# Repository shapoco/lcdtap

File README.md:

A library and its example design that receives LCD controller commands (via SPI or I2C)
and outputs the framebuffer as a DVI-D signal.

## Overview

See [introduction page](https://shapoco.github.io/lcdtap/).

## Implementations

### [LcdTap-Pico2 Universal](example/pico2_universal/)

Supports multiple LCD controllers (ST7789, ILI9341, SSD1306, SSD1331, ST7032)
and interfaces, selectable at runtime via an OSD menu.

### [LcdTap-Pico2W Remote](example/pico2w_remote/)

Raspberry Pi Pico 2 W version with no video output: the captured screen is
read over WiFi through an HTTP JSON API and a built-in web UI
(`http://lcdtap.local/`). WiFi setup via the
[Remote Setup page](https://shapoco.github.io/lcdtap/remote/) (WebSerial).

## License

MIT License — see [LICENSE](LICENSE).

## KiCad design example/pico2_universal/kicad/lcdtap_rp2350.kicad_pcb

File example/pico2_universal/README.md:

# LcdTap-Pico2 Universal

A universal LCD-to-DVI converter example for Raspberry Pi Pico 2. With an OSD (On-Screen Display) menu for runtime configuration.

## Features

- Supports four input interfaces selectable via OSD: I2C, 4-Line SPI, 3-Line SPI, 8-bit Parallel
- Runtime configuration via OSD menu: interface, controller type, pixel format, LCD size, inversion, R/B swap, rotation, scale mode
- Settings (including selected interface) saved to flash on Apply and restored at next boot
- DVI output: 640×480@60Hz or 1280×720@30Hz selectable via GPIO21 at boot
- Composite video output (NTSC/PAL) on otherwise-unused GPIOs, selectable from the OSD: a 1-pin PWM DAC or a 7-bit R-2R ladder
- DisplayLink output: drives a USB graphics adapter (DisplayLink DL-1x0/1x5) at 1280×720 or 1920×1080@60Hz via a PIO USB Full-Speed host on GPIO10/11 (best-effort update rate)
- USB CDC serial interface for remote configuration and framebuffer readout from a PC or smartphone

> [!WARNING]
> Parallel Mode has not been tested yet. Please let me know if it works!

## Schematics

- Keep the input bus as short as possible and ensure all cables are the same length.
- See also: [Recommended Header Pinout](https://shapoco.github.io/lcdtap/#header_pinout)

## GPIO Assignments

### Common (all modes)

| GPIO  | Direction | Name | Active-low | Internal Pull-up | Description |
|:--:|:--:|:--|:--:|:--:|:--|
| 0     | IN        | RST | v | v | LCD Hardware reset (SPI mode) |
| 5–11  | OUT       | CVBS_D[0..6] | | | Composite R-2R ladder (SPI modes only, when selected) |
| 10    | OUT       | CVBS_PWM | | | Composite PWM output (SPI/I2C, when selected) |
| 10/11 | I/O       | USB_DP / USB_DM | | | DisplayLink USB host D+/D- (SPI/I2C, when selected) |
| 12–19 | OUT       | (DVI signals) | | | RP2350 HSTX |
| 20    | IN        | CFG_OUT_RESO_SEL | v | v | High=640×480@60Hz,<br>Low=1280×720@30Hz |
| 21    | IN        | KEY_DOWN | v | v | Low=pressed |
| 22    | IN        | KEY_LEFT | v | v | Low=pressed |
| 26    | IN        | KEY_UP | v | v | Low=pressed |
| 27    | IN        | KEY_RIGHT | v | v | Low=pressed |
| 28    | IN        | KEY_ENTER | v | v | Low=pressed |

### I2C Mode

| GPIO  | Direction | Name | Active-low | Internal Pull-up | Description |
|:--:|:--:|:--|:--:|:--:|:--|
| 8     | IN        | SDA | | v | I2C data |
| 9     | IN        | SCL | | v | I2C clock |

### 4-Line/3-Line SPI Mode

| GPIO  | Direction | Name | Active-low | Internal Pull-up | Description |
|:--:|:--:|:--|:--:|:--:|:--|
| 1     | IN        | CS | v | v | LCD Chip select |
| 2     | IN        | SCLK | | | SPI clock from master |
| 3     | IN        | MOSI | | | SPI data from master |
| 4     | IN        | DC | | | D/C# signal from master (4-line mode only) |

### Parallel Mode

| GPIO  | Direction | Name | Active-low | Internal Pull-up | Description |
|:--:|:--:|:--|:--:|:--:|:--|
| 1 | IN | CS | v | v | LCD Chip select|
| 2 | IN | WR | | | Write strobe |
| 3–10 | IN | D[0..7] | | | parallel data |
| 11 | IN | DC | | | D/C# signal |

For text displays, connect the R/W signal to CS and the E signal to WR.

For KS0108-compatible displays (such as SG12864), connect CS1 to RST,
CS2 to CS, and AND the inverted R/W signal with the E signal to connect to WR.
If R/W is fixed to Low, you can connect the E signal directly to the WR terminal.

## Composite Video Output (NTSC/PAL)

The HDMI connector occupies GPIO12–19, so composite video uses the GPIOs that
the input bus leaves free. Two independent OSD items control it (or
`outputInterface` / `compositeDac` over USB CDC):

- **`Output`** — `DVI-D`, `NTSC` or `PAL`
- **`Composite DAC`** — `PWM` or `R-2R`

There are therefore two quality tiers, and you only build the one you want:

| DAC | GPIO | Parts | Picture | Buses |
|:--|:--|:--|:--|:--|
| **PWM** | 10 | 1 resistor + 1 capacitor | ~12 luma steps, ~70% amplitude | SPI, I2C |
| **R-2R** | 5–11 | 14 resistors, no buffer | 7-bit luma, full amplitude | SPI only |

The R-2R ladder spans GPIO5–11, which covers the I2C pins (GPIO8/9), so it is
selectable only on SPI; the OSD greys it out otherwise. Composite output is
unavailable on the parallel bus entirely — GPIO3–10 are data lines there, which
covers the PWM pin too.

**The device resets** when `Output` changes (each mode needs a different system
clock), and when the bus or the DAC changes while a composite mode is running.

PAL colour is not implemented yet; PAL currently outputs monochrome on both
DACs.

> [!NOTE]
> Both DACs share GPIO10, so the two circuits are alternative populations, not
> simultaneous ones. Build whichever tier you want.

### PWM DAC — simple tier

One GPIO, one resistor, one capacitor. No buffer.

```
GPIO10 --- R ---+--- RCA centre
                |
                C
                |
               GND
```

The PWM period equals the sample period, so the duty resolution *is* the
sample period in system clocks: 22 steps on NTSC, 17 on PAL. White sits at
duty 17/22 rather than 100%, because chroma overshoots white by up to
+133 IRE and has to fit above it.

That, plus the 12 mA per-pin limit, is why the amplitude falls short of the
1 V standard — a single 3.3 V GPIO simply cannot reach it:

| R | White level | Sync amplitude | Peak current |
|:--|:--|:--|:--|
| 120 Ω | 0.78 V (78%) | 0.23 V (80%) | 13.5 mA |
| **150 Ω** | **0.70 V (70%)** | **0.21 V (72%)** | **12.0 mA** |
| 180 Ω | 0.63 V (63%) | 0.18 V (64%) | 10.8 mA |

Start at **R = 150 Ω** and drop to 120 Ω if a receiver refuses to lock.
Most TVs slice sync on the AC-coupled signal and tolerate this; capture
devices are less forgiving. C = 100–470 pF (corner ≈ 5–6 MHz).

The PWM carrier sits at 14.3 MHz with chroma at 3.58 MHz — only two octaves
apart — so a single-pole RC leaves visible carrier ripple. That is the
accepted cost of this tier.

### R-2R ladder — quality tier

The ladder drives the 75 Ω line **directly, with no buffer**. To deliver the
~1 V composite range into 75 Ω, its output impedance has to be low, so the
resistors are ~10× smaller than a textbook ladder: **R = 100 Ω series, 2R =
200 Ω rungs, 200 Ω termination.**

The firmware drives GPIO5 as the **LSB** and GPIO11 as the **MSB** (the PIO
maps sample bit 0 to the lowest GPIO). In an R-2R ladder the bit nearest the
output node has the greatest weight, so the **output is tapped at the GPIO11
(MSB) end** and the termination sits at the GPIO5 (LSB) end. Sync tip is 0 V at
the ladder, so it connects straight to the RCA centre — no coupling capacitor.

```
GPIO11 -- 200R --+---------------- RCA centre       (MSB, weight 64)
        (MSB)    |            |
               100R        (470pF)   optional reconstruction
                |            |        cap to GND (~6 MHz)
GPIO10 -- 200R --+          GND
                 :   (GPIO9, 8, 7, 6 identical)
               100R
                |
GPIO5  -- 200R --+                                  (LSB, weight 1)
        (LSB)    |
               200R    (2R termination)
                |
               GND
```

Wiring it the other way round — output at GPIO5, termination at GPIO11 —
reverses the bit weights and scrambles the picture, so double-check the
orientation.

2R = 200 Ω keeps the exact 2:1 R-2R ratio against the 100 Ω series resistor,
and in practice gives the most stable picture. The termination is another
200 Ω, so every rung and the termination share the same value.

Peak GPIO current is ~13 mA — just over the nominal 12 mA, which is fine here.
The drive strength stays at 12 mA (set in firmware).

> [!NOTE]
> These are a bench starting point. With a scope on a **50 % grey** field,
> confirm the mid-scale step is clean and monotonic.
>
> With nominal values the levels come out a few percent high (full scale
> ~1.4 V, white ~1.1 V, blanking ~0.3 V; sync tip 0 V). Trim this by scaling
> all three resistor families up together, or just leave it — the receiver
> works on relative levels. **Do not** retune it with `lvlWhite` / `lvlBlank`
> in `composite_timing.cpp`: those are shared with the PWM DAC. Use 1 %
> resistors, and keep 2R = 200 and the termination = 200 as a matched set.

## DisplayLink Output (USB)

Select `DisplayLink` as the `Output` (or `outputInterface = 3` over USB CDC) to
drive a USB graphics display adapter instead of the HDMI connector. The
adapter is driven by a PIO-based USB **Full-Speed** host
([Pico_USB_Disp](https://github.com/htlabnet/Pico_USB_Disp)) on GPIO10 (D+)
and GPIO11 (D−), so only the **DisplayLink DL-1x0 / DL-1x5** generation
works — newer chips (DL-3xxx and later) require High-Speed and encrypted
protocols. 1920×1080 needs a DL-165 or DL-195; smaller chips automatically
fall back to 1280×720.

- **Resolution** follows the CFG_OUT_RESO_SEL pin: open = 1280×720@60Hz,
  low = 1920×1080@60Hz (the DVI 480p/720p slots map to 720p/1080p).
- The adapter scans out a stable 60 Hz signal from its own framebuffer; the
  Pico streams **best-effort partial updates** over the ~1 MB/s bulk link.
  Only lines whose pixel values actually changed are re-sent, so mostly
  static screens update quickly; a full-screen change takes on the order of
  0.3–1 s (tearing can occur — there is no vsync over USB).
- Unavailable on the parallel bus (GPIO10/11 are D[7] and D/C# there), and
  mutually exclusive with the composite DACs, which share GPIO10.

Hardware: wire a USB-A receptacle with **5 V bus power (500 mA class)** to
the adapter, D+/D− to GPIO10/11. The 3.3 V GPIO levels match USB FS
signalling directly; series damping resistors up to ~47 Ω are tolerable at
Full-Speed (22–27 Ω preferred).

## Uploading Firmware

1. Download zip file from [releases](https://github.com/shapoco/lcdtap/releases).
2. Extract `lcdtap_pico2_universal.uf2` from the zip file.
3. Connect the Pico 2 to your computer while holding the BOOTSEL button to enter bootloader mode.
4. Copy the UF2 file to the mounted drive.

## OSD Menu

Press the Enter key to open the configuration menu.

| Key | Action |
|-----|--------|
| Up / Down | Navigate menu items |
| Left / Right | Adjust selected value |
| Enter on Apply | Apply changes and save to flash |
| Enter on Cancel | Discard changes and close |
| Enter on Command Dump | Open the command dump viewer |

### Command Dump Viewer

Selecting **Command Dump** opens a hex viewer that shows the raw LCD command/data stream captured since power-on (or since the last trigger).

| Key | Action |
|-----|--------|
| Enter | Clear buffer and start a new capture |
| Right | Stop capture (mark complete) |
| Left | Return to the configuration menu |
| Up / Down | Scroll |

Each row displays 16 entries. Colors indicate the type of each entry:

| Color | Meaning |
|-------|---------|
| Black on cyan | Command byte |
| White on black / dark-gray (alternating) | Data byte |
| Black on yellow (`HR`) | Hardware reset event |
| `..` in dark gray | Empty (not yet captured) |

## USB Serial Interface

LcdTap-Pico2 Universal accepts JSON commands over the USB CDC serial interface.
This allows remote configuration and framebuffer readout from a PC.

Available here: https://shapoco.github.io/lcdtap/monitor

## Building Firmware from Source

```bash
export PICO_SDK_PATH=/path/to/pico-sdk
./build.sh
```

The UF2 file is generated at `build/lcdtap_pico2_universal.uf2`.

### CMake Options

| Option | Default | Description |
|--------|---------|-------------|
| `LCDTAP_LCD_SIZE_W` | 240 | Initial LCD framebuffer width (px) |
| `LCDTAP_LCD_SIZE_H` | 320 | Initial LCD framebuffer height (px) |

Example:

```bash
cmake .. -DCMAKE_BUILD_TYPE=Release -DPICO_BOARD=pico2 \
         -DLCDTAP_LCD_SIZE_W=320 -DLCDTAP_LCD_SIZE_H=240
```

## External Deserializer for High-Speed SPI

The SPI interface of LcdTap-Pico2 Universal can support clock frequencies up to approximately 50MHz. For frequencies exceeding this, you can add an external deserializer outside the Pico2 to support higher speeds. In this case, select Parallel as the Interface in the OSD menu.

## Troubleshooting

### Failed to boot normally

Try powering on or resetting while pressing the Left key. This will boot while ignoring the settings saved in flash.

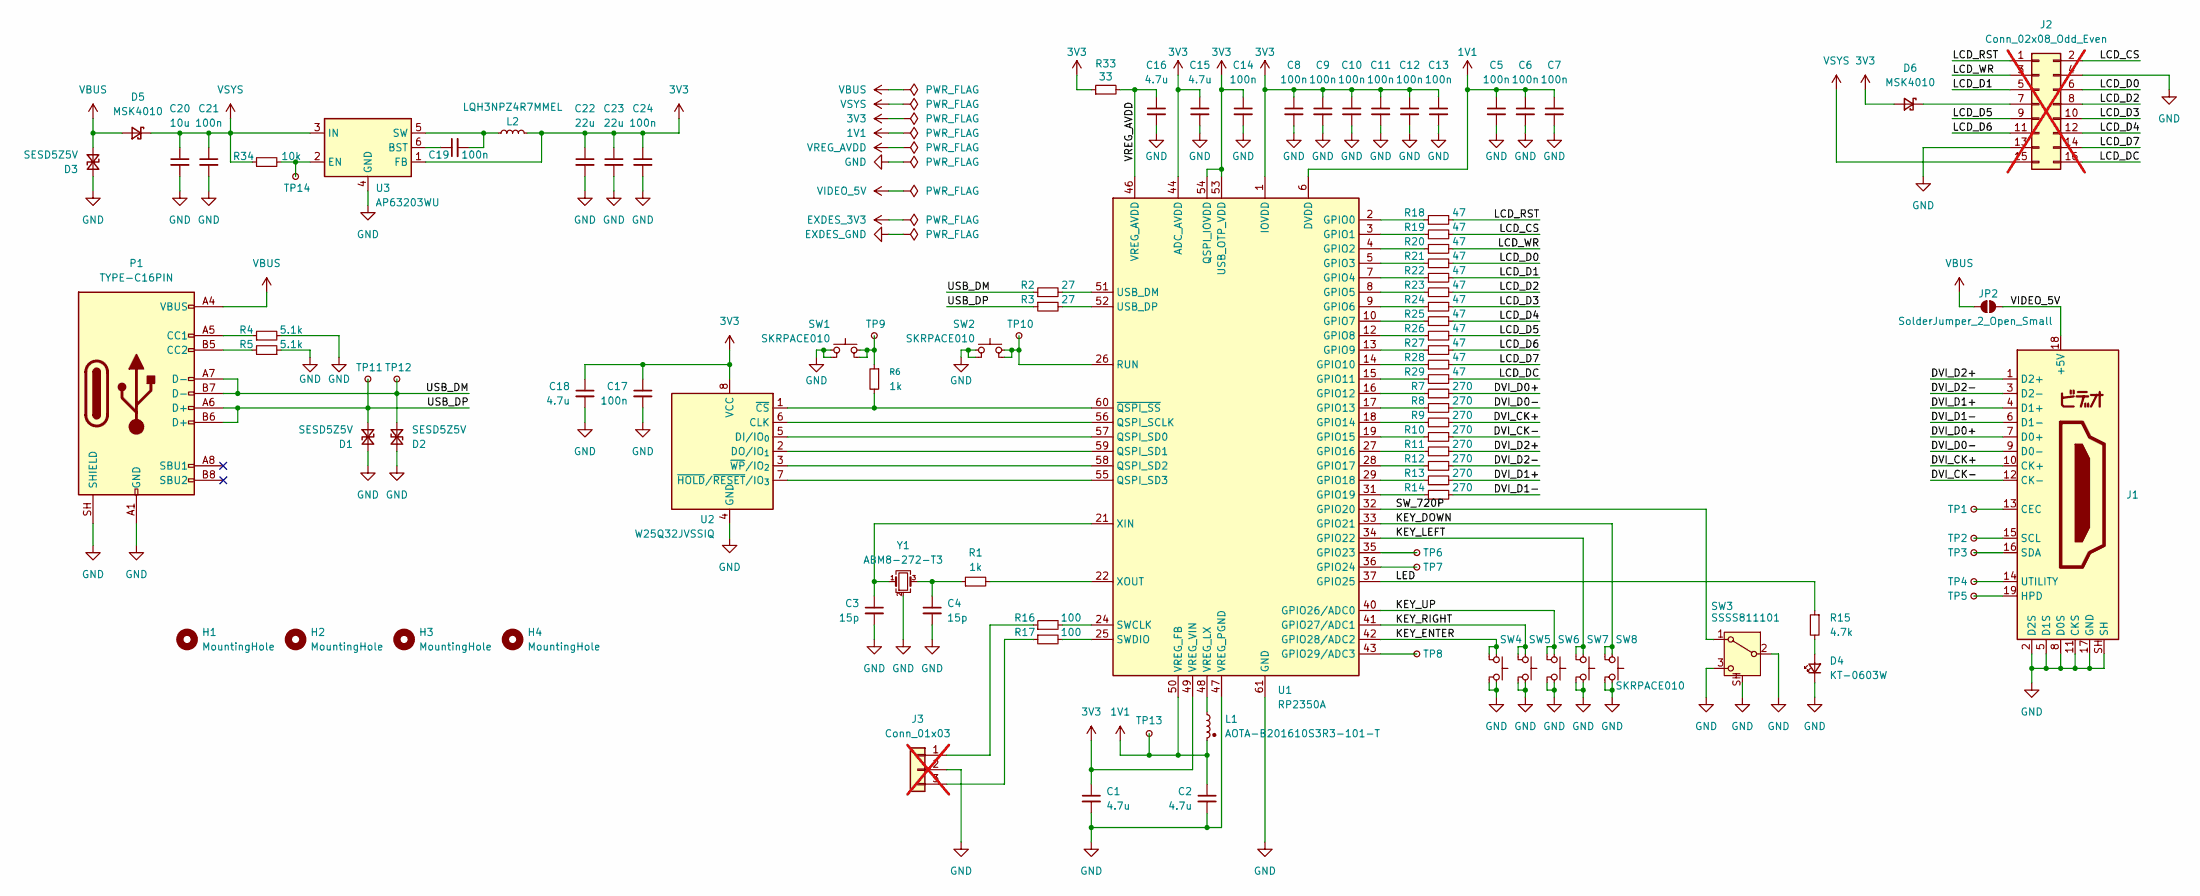
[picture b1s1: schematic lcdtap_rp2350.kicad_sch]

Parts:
C1, C2, C15, C16, C18: 4.7u; C_0603_1608Metric; LCSC C19666
C3, C4: 15p; C_0402_1005Metric; LCSC C1548
C5, C6, C7, C8, C9, C10, C11, C12, C13, C14, C17, C19, C21, C24: 100n; C_0402_1005Metric; LCSC C1525
C20: 10u; C_0603_1608Metric; LCSC C19702
C22, C23: 22u; C_0603_1608Metric; LCSC C59461
D1, D2, D3: SESD5Z5V; D_SOD-523; LCSC C19631222
D4: KT-0603W; LED_0603_1608Metric; LCSC C2290
D5, D6: MSK4010; D_SOD-523; LCSC C282563
H1, H2, H3, H4: MountingHole; MountingHole_3.5mm
J1: HDMI-001S; HDMI_A_Molex_208658-1001_Horizontal_Edge; LCSC C720616
J2: Conn_02x08_Odd_Even; PinHeader_2x08_P2.54mm_Horizontal_Rev; not fitted
J3: Conn_01x03; PinHeader_1x03_P2.54mm_Vertical; not fitted
JP2: SolderJumper_2_Open_Small; SolderJumper-2_P1.3mm_Open_RoundedPad1.0x1.5mm
L1: AOTA-B201610S3R3-101-T; LCSC C42411119
L2: LQH3NPZ4R7MMEL; LCSC C527613
P1: TYPE-C16PIN; USB_C_Receptacle_HCTL_HC-TYPE-C-16P-01A; LCSC C393939
R1, R6: 1k; R_0402_1005Metric; LCSC C11702
R2, R3: 27; R_0402_1005Metric; LCSC C25100
R4, R5: 5.1k; R_0402_1005Metric; LCSC C25905
R7, R8, R9, R10, R11, R12, R13, R14: 270; R_0402_1005Metric; LCSC C25155
R15: 4.7k; R_0402_1005Metric; LCSC C25900
R16, R17: 100; R_0402_1005Metric; LCSC C25076
R18, R19, R20, R21, R22, R23, R24, R25, R26, R27, R28, R29: 47; R_0402_1005Metric; LCSC C25118
R33: 33; R_0402_1005Metric; LCSC C25105
R34: 10k; R_0402_1005Metric; LCSC C25744
SW1, SW2, SW4, SW5, SW6, SW7, SW8: SKRPACE010; SW_Push_1P1T_NO_Vertical_Wuerth_434133025816; LCSC C139797
SW3: SSSS811101; SW_SPDT_Alps_SSSS811101; LCSC C109335
TP1, TP2, TP3, TP4, TP5, TP6, TP7, TP8, TP9, TP10, TP11, TP12, TP13, TP14: TestPoint_Small; TestPoint_Pad_D1.0mm
U1: RP2350A; QFN-60-1EP_7x7mm_P0.4mm_EP3.4x3.4mm; LCSC C42411118
U2: W25Q32JVSSIQ; SOIC-8_5.3x5.3mm_P1.27mm; LCSC C179173
U3: AP63203WU; TSOT-23-6; LCSC C780769
Y1: ABM8-272-T3; Crystal_SMD_3225-4Pin_3.2x2.5mm; LCSC C20625731

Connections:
1V1: C2.1, C5.1, C6.1, C7.1, L1.1, TP13.1 (1_1), U1.6 (DVDD), U1.23 (DVDD), U1.39 (DVDD), U1.50 (VREG_FB)
3V3: C1.1, C8.1, C9.1, C10.1, C11.1, C12.1, C13.1, C14.1, C15.1, C17.1, C18.1, C22.1, C23.1, C24.1, D6.2 (A), L2.1, R33.1, U1.1 (IOVDD), U1.11 (IOVDD), U1.20 (IOVDD), U1.30 (IOVDD), U1.38 (IOVDD), U1.44 (ADC_AVDD), U1.45 (IOVDD), U1.49 (VREG_VIN), U1.53 (USB_OTP_VDD), U1.54 (QSPI_IOVDD), U2.8 (VCC), U3.1 (FB)
/DVI_CK+: J1.10 (CK+), R9.2
/DVI_CK-: J1.12 (CK-), R10.2
/DVI_D0+: J1.7 (D0+), R7.2
/DVI_D0-: J1.9 (D0-), R8.2
/DVI_D1+: J1.4 (D1+), R13.2
/DVI_D1-: J1.6 (D1-), R14.2
/DVI_D2+: J1.1 (D2+), R11.2
/DVI_D2-: J1.3 (D2-), R12.2
/KEY_DOWN: SW8.2, U1.33 (GPIO21)
/KEY_ENTER: SW4.2, U1.42 (GPIO28/ADC2)
/KEY_LEFT: SW7.2, U1.34 (GPIO22)
/KEY_RIGHT: SW5.2, U1.41 (GPIO27/ADC1)
/KEY_UP: SW6.2, U1.40 (GPIO26/ADC0)
/LCD_CS: J2.2, R19.2
/LCD_D0: J2.6, R21.2
/LCD_D1: J2.5, R22.2
/LCD_D2: J2.8, R23.2
/LCD_D3: J2.10, R24.2
/LCD_D4: J2.12, R25.2
/LCD_D5: J2.9, R26.2
/LCD_D6: J2.11, R27.2
/LCD_D7: J2.14, R28.2
/LCD_DC: J2.16, R29.2
/LCD_RST: J2.1, R18.2
/LCD_WR: J2.3, R20.2
/LED: R15.1, U1.37 (GPIO25)
/SW_720P: SW3.1 (A), U1.32 (GPIO20)
/USB_DM: D2.1 (A1), P1.A7 (D-), P1.B7 (D-), R2.1, TP12.1 (1_1)
/USB_DP: D1.1 (A1), P1.A6 (D+), P1.B6 (D+), R3.1, TP11.1 (1_1)
GND: C1.2, C2.2, C3.2, C4.2, C5.2, C6.2, C7.2, C8.2, C9.2, C10.2, C11.2, C12.2, C13.2, C14.2, C15.2, C16.2, C17.2, C18.2, C20.2, C21.2, C22.2, C23.2, C24.2, D1.2 (A2), D2.2 (A2), D3.2 (A2), D4.1 (K), J1.2 (D2S), J1.5 (D1S), J1.8 (D0S), J1.11 (CKS), J1.17 (GND), J1.SH, J2.4, J2.13, J3.2, P1.A1 (GND), P1.A12 (GND), P1.B1 (GND), P1.B12 (GND), P1.SH (SHIELD), R4.2, R5.1, SW1.1, SW2.1, SW3.2 (B), SW3.3 (C), SW3.SH, SW4.1, SW5.1, SW6.1, SW7.1, SW8.1, U1.47 (VREG_PGND), U1.61 (GND), U2.4 (GND), U3.4 (GND), Y1.2 (G), Y1.4 (G)
unnamed: C4.1, R1.1, Y1.3
unnamed: D4.2 (A), R15.2
unnamed: D6.1 (K), J2.7
unnamed: J1.13 (CEC), TP1.1 (1_1)
unnamed: J1.19 (HPD), TP5.1 (1_1)
unnamed: J1.15 (SCL), TP2.1 (1_1)
unnamed: J1.16 (SDA), TP3.1 (1_1)
unnamed: J1.14 (UTILITY), TP4.1 (1_1)
unnamed: J3.1, R16.1
unnamed: J3.3, R17.1
unnamed: P1.A5 (CC1), R4.1
unnamed: P1.B5 (CC2), R5.2
unnamed: R6.1, SW1.2, TP9.1 (1_1)
unnamed: R18.1, U1.2 (GPIO0)
unnamed: R19.1, U1.3 (GPIO1)
unnamed: R20.1, U1.4 (GPIO2)
unnamed: R21.1, U1.5 (GPIO3)
unnamed: R22.1, U1.7 (GPIO4)
unnamed: R23.1, U1.8 (GPIO5)
unnamed: R24.1, U1.9 (GPIO6)
unnamed: R25.1, U1.10 (GPIO7)
unnamed: R26.1, U1.12 (GPIO8)
unnamed: R27.1, U1.13 (GPIO9)
unnamed: R28.1, U1.14 (GPIO10)
unnamed: R29.1, U1.15 (GPIO11)
unnamed: R7.1, U1.16 (GPIO12)
unnamed: R8.1, U1.17 (GPIO13)
unnamed: R9.1, U1.18 (GPIO14)
unnamed: R10.1, U1.19 (GPIO15)
unnamed: R11.1, U1.27 (GPIO16)
unnamed: R12.1, U1.28 (GPIO17)
unnamed: R13.1, U1.29 (GPIO18)
unnamed: R14.1, U1.31 (GPIO19)
unnamed: TP6.1 (1_1), U1.35 (GPIO23)
unnamed: TP7.1 (1_1), U1.36 (GPIO24)
unnamed: TP8.1 (1_1), U1.43 (GPIO29/ADC3)
unnamed: U1.56 (QSPI_SCLK), U2.6 (CLK)
unnamed: U1.57 (QSPI_SD0), U2.5 (DI/IO_{0})
unnamed: U1.59 (QSPI_SD1), U2.2 (DO/IO_{1})
unnamed: U1.58 (QSPI_SD2), U2.3 (~WP/IO_{2})
unnamed: U1.55 (QSPI_SD3), U2.7 (~HOLD/~RESET/IO_{3})
unnamed: SW2.2, TP10.1 (1_1), U1.26 (RUN)
unnamed: R16.2, U1.24 (SWCLK)
unnamed: R17.2, U1.25 (SWDIO)
unnamed: R2.2, U1.51 (USB_DM)
unnamed: R3.2, U1.52 (USB_DP)
unnamed: L1.2, U1.48 (VREG_LX)
unnamed: C3.1, U1.21 (XIN), Y1.1
unnamed: R1.2, U1.22 (XOUT)
unnamed: R6.2, U1.60 (~QSPI_SS), U2.1 (~CS)
unnamed: C19.1, U3.6 (BST)
unnamed: R34.2, TP14.1 (1_1), U3.2 (EN)
unnamed: C19.2, L2.2, U3.5 (SW)
VBUS: D3.1 (A1), D5.2 (A), JP2.1 (A), P1.A4 (VBUS), P1.A9 (VBUS), P1.B4 (VBUS), P1.B9 (VBUS)
VIDEO_5V: J1.18 (+5V), JP2.2 (B)
VREG_AVDD: C16.1, R33.2, U1.46 (VREG_AVDD)
VSYS: C20.1, C21.1, D5.1 (K), J2.15, R34.1, U3.3 (IN)

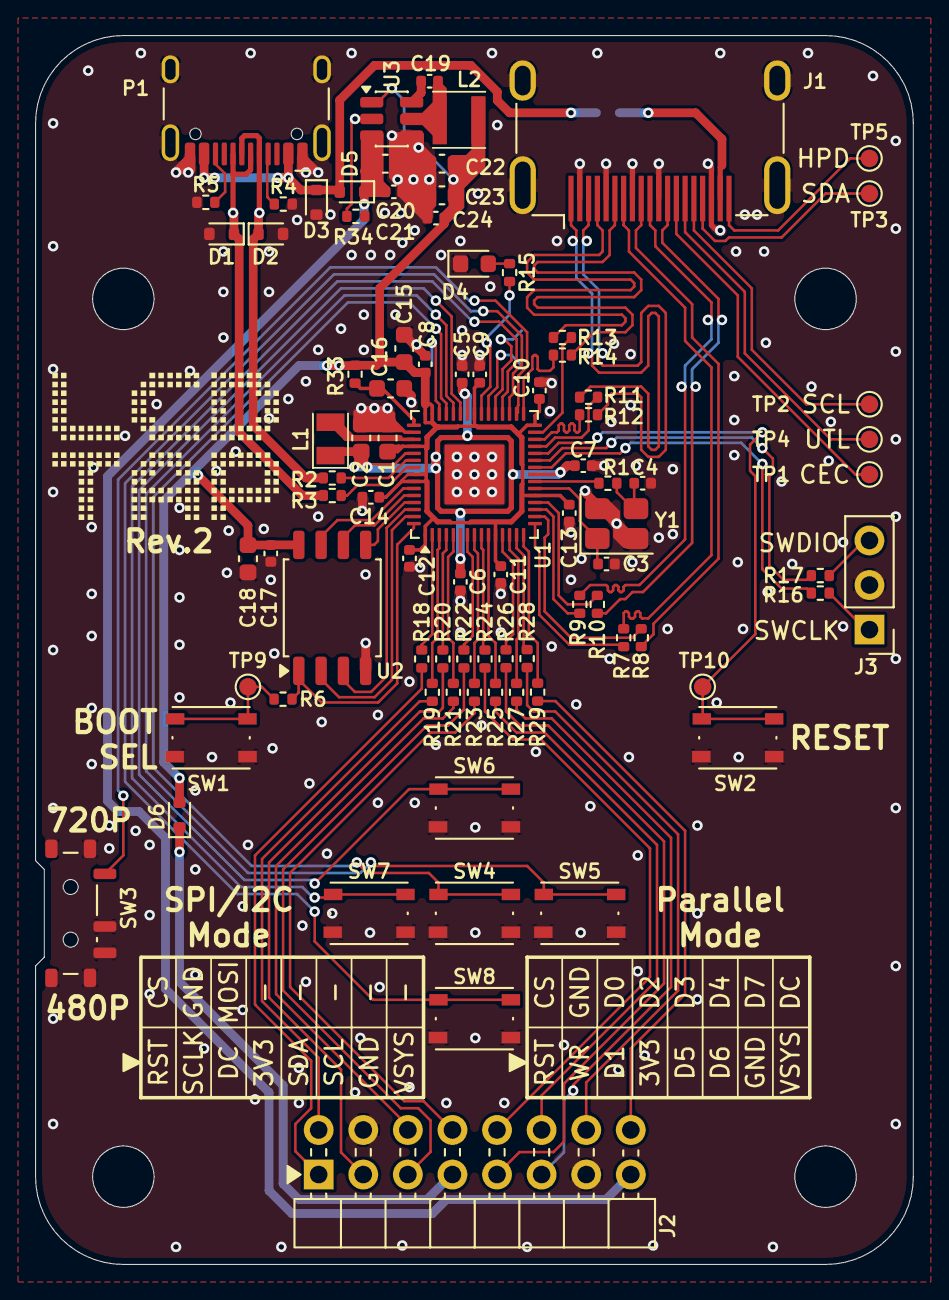
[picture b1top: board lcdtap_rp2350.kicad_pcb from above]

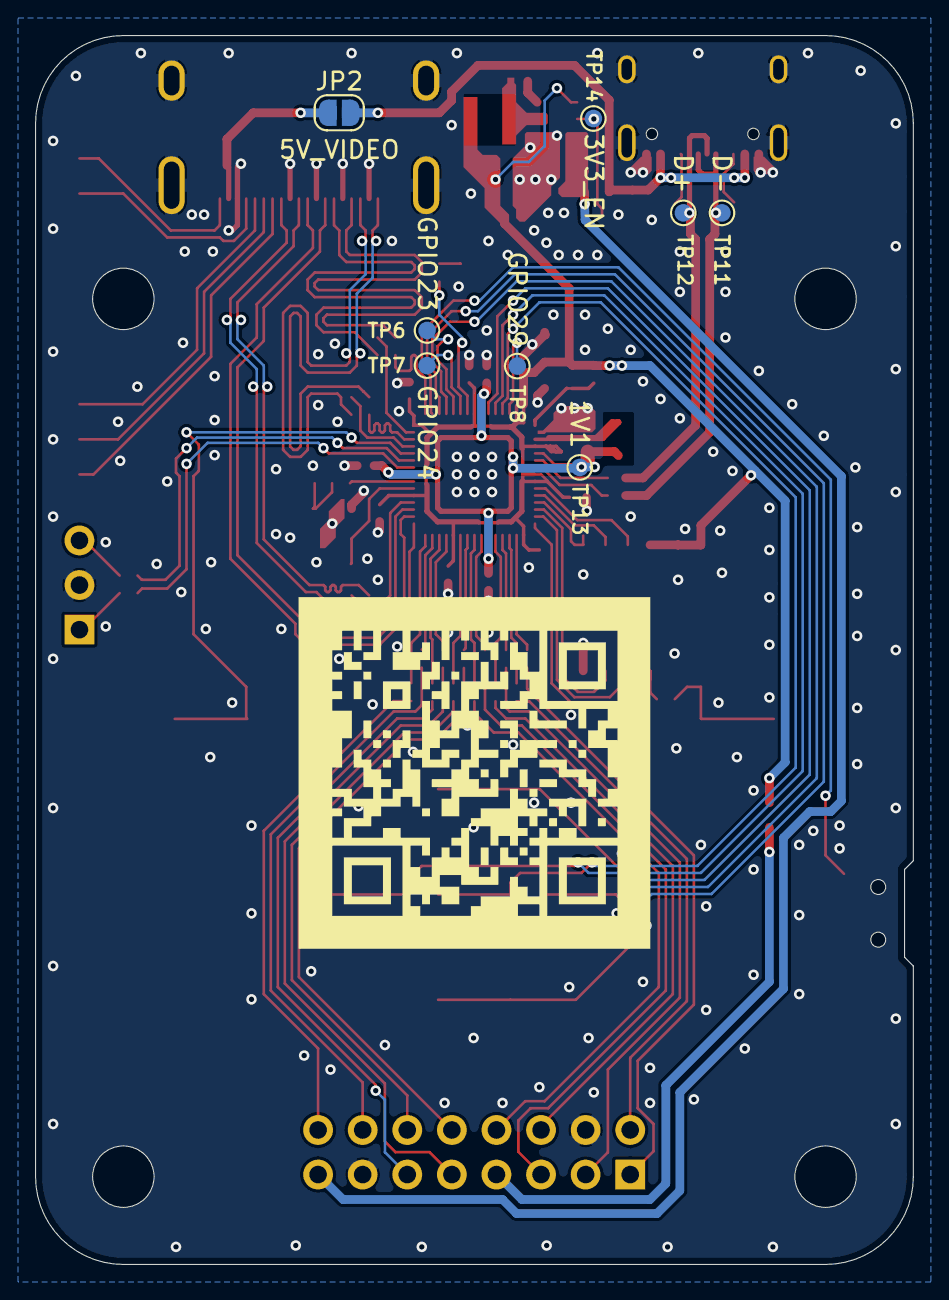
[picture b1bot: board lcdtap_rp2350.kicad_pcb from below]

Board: 2 copper layers, 50.0 x 70.0 mm, 98 parts (8 on the bottom side), 89 nets.

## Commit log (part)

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2026-05-09 fix frame buffer format from RGB888 to RGB565
2026-05-10 change SPI input from serial to parallel
2026-05-11 fix comment
2026-05-11 fix data latch timing
2026-05-12 Change library name from SpiLcd2Dvi to LcdTap
2026-05-12 fix lcdtap::Controller --> lcdtap::ControllerType
2026-05-12 lib: add setOutputRotation() for DVI output rotation
2026-05-12 example: replace scale-mode GPIO with output rotation (GPIO26/27)
2026-05-12 fix README
2026-05-12 example/pico2_ssd1309: invert INPUT_MODE polarity (LOW=I2C default)
2026-05-13 change SPI BCLK edge from falling to rising
2026-05-13 improve performance
2026-05-13 fix comment and documents
2026-05-13 add schematic
2026-05-13 fix schematic
2026-05-14 fix comment language
2026-05-14 change "SSD1309" to "SSD1306"
2026-05-14 schematic added for SSD1306
2026-05-14 add binary download link
2026-05-15 fix schematics
2026-05-15 fix release script
2026-05-16 fix font
2026-05-16 fix pixel format changing
2026-05-16 removed example app pico2_3line_spi
2026-05-17 fix behavior of LcdTap::updateConfig
2026-05-18 fix OSD UI
2026-05-19 - rename PixelFormat --> InterfaceFormat - remove PixelFormat(InterfaceFormat) from OSD Menu - rename Members of PixelFormat(InterfaceFormat)
2026-05-20 Fix CS glitch issues
2026-05-21 fix rotation for SSD1306, SSD1331
2026-05-21 add recommended header pinout
2026-05-21 fix figures
2026-05-21 fix header pinout
2026-05-22 fix parallel interface
2026-05-22 add high-speed SPI support instruction
2026-05-22 add quick rotation function
2026-05-23 add USB feature
2026-05-23 fix USB mode: update volume serial
2026-05-23 - Rename identifiers to match coding rules - Change OSD to set APPLY as selected when pressing Enter on BOOL, ENUM, or INTEGER type items - Enter USB storage mode if down key is pressed at startup
2026-05-23 remove volume serial update
2026-05-23 move menu item
2026-05-23 remove USB storage mode
2026-05-24 OsdMenuItem::values --> OsdMenuItem::options
2026-05-24 fix settings.json for Claude
2026-05-24 add preset load function and write protected option to web app
2026-05-25 Ignore FlashROM settings if left key is pressed at startup
2026-05-29 add KiCad project for RP2350
2026-05-31 PCB artwork draft
2026-06-01 fix PCB
2026-06-02 PCB rev.1 ordered
2026-06-02 add JLCPCB order memo
2026-06-12 PCB rev.2
2026-06-13 add enclosure model
2026-06-13 fix enclosure
2026-06-13 add WebUSB support
2026-06-13 fix number of InterfaceFormat
2026-06-14 add pixel format override
2026-06-14 file moved
2026-06-14 add CASET/RASET value range guard
2026-06-14 add configuration instruction for SOEKS-01M and J7-c
2026-06-15 file move
2026-06-15 fix script
2026-06-20 - Add new APIs for accessing configuration structures - Add new APIs for retrieving presets - Refactor OSD menu to use the new configuration APIs - Add trimming functionality for devices that use onl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
2026-06-20 fix trimming
2026-06-20 fix make_release.sh
2026-06-20 preset added
2026-06-21 fix preset
2026-06-21 fix preset description
2026-06-21 fix stamp widget
2026-06-22 add preset for PicoPad
2026-06-22 fix race condition
2026-06-23 change scaling mode
2026-06-23 fix glich
2026-06-23 fix LcdTap::fillScanline
2026-06-23 optimize OSD
2026-06-24 optimize scaling
2026-06-26 config.hpp/cpp added
2026-06-26 preset description added
